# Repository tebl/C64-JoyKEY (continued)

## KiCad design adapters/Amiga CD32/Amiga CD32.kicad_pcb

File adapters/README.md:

# Adapters
Instead of adding a ton of jumpers to the module with the aim of accounting for every system known to man, I instead chose to leave those details up to the adapter. For more specific information, see the [adapters](https://github.com/tebl/C64-JoyKEY/blob/main/documentation/adapters.md) document available as part of the documentation (mostly to avoid having to maintain two copies of the same information).

For BOM, parts needed on putting it together is found in the relevant subfolder READMEs.

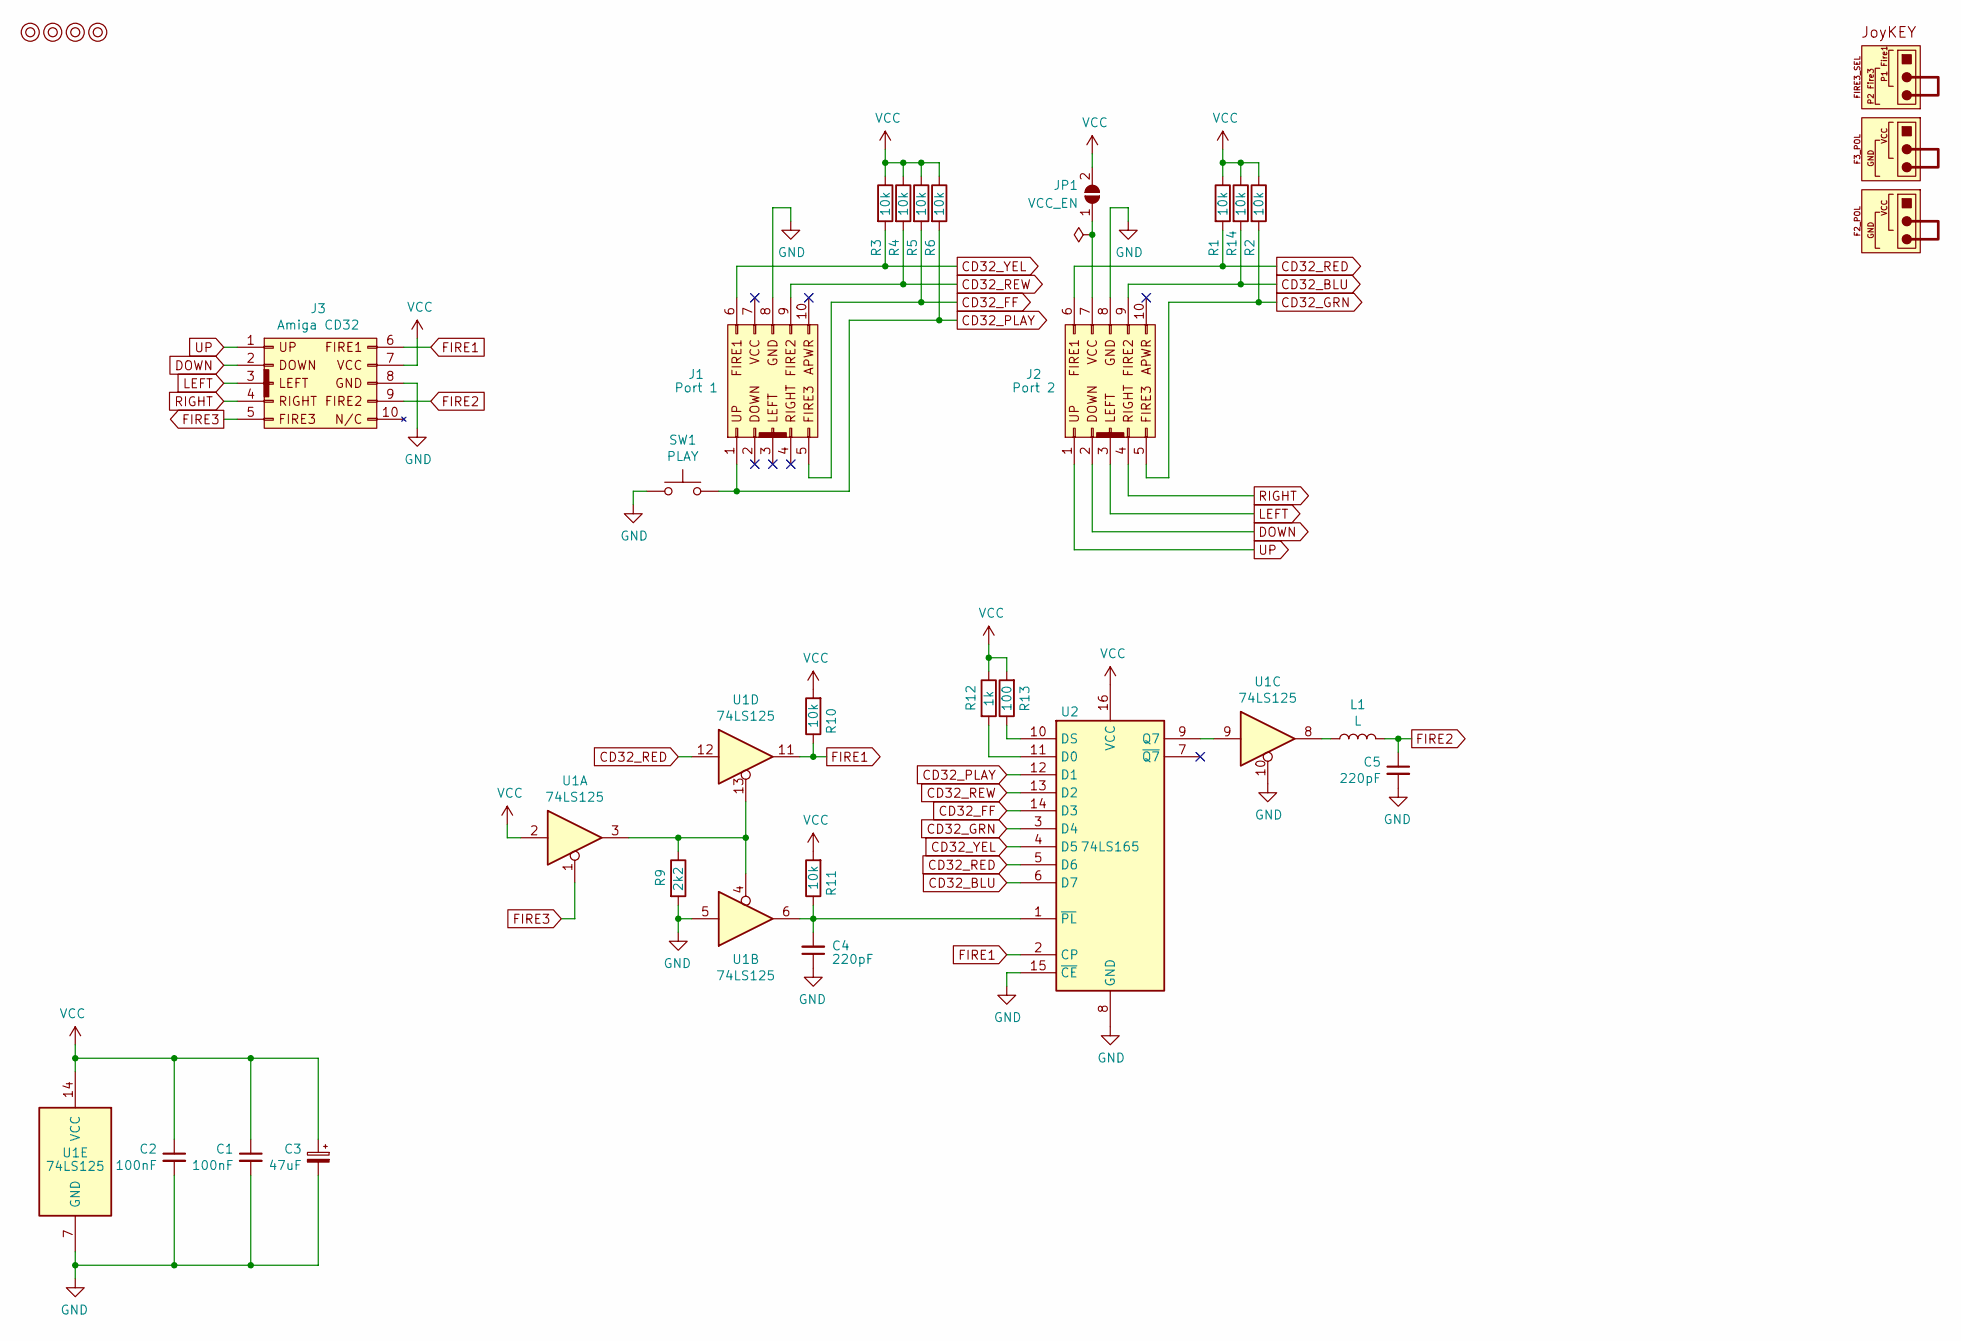
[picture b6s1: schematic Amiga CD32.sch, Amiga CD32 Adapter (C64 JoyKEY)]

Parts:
C1, C2: 100nF; C_Disc_D4.7mm_W2.5mm_P5.00mm
C3: 47uF; CP_Radial_D5.0mm_P2.00mm
C4, C5: 220pF; C_Disc_D4.7mm_W2.5mm_P5.00mm
J1: Port 1; IDC_Joystick
J2: Port 2; IDC_Joystick
J3: Amiga CD32; IDC_Joystick
JP1: VCC_EN; bridge_r
L1: L; L_Axial_L6.6mm_D2.7mm_P10.16mm_Horizontal_Vishay_IM-2
M1, M2, M3, M4: Mounting; M3_pin
R1, R3, R4, R11, R14: 10k; R_Axial_DIN0207_L6.3mm_D2.5mm_P10.16mm_Horizontal
R2, R5, R6, R10: 10k; R_Axial_DIN0207_L6.3mm_D2.5mm_P7.62mm_Horizontal
R9: 2k2; R_Axial_DIN0207_L6.3mm_D2.5mm_P7.62mm_Horizontal
R12: 1k; R_Axial_DIN0207_L6.3mm_D2.5mm_P7.62mm_Horizontal
R13: 100; R_Axial_DIN0207_L6.3mm_D2.5mm_P7.62mm_Horizontal
SW1: PLAY; SW_PUSH_6mm
U1: 74LS125; DIP-14_W7.62mm_Socket_LongPads
U2: 74LS165; DIP-16_W7.62mm_Socket_LongPads

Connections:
CD32_BLU: J2.9, R14.2, U2.6 (D7)
CD32_FF: J1.5, R5.2, U2.14 (D3)
CD32_GRN: J2.5, R2.2, U2.3 (D4)
CD32_PLAY: J1.1, R6.2, SW1.2, U2.12 (D1)
CD32_RED: J2.6, R1.2, U1.12, U2.5 (D6)
CD32_REW: J1.9, R4.2, U2.13 (D2)
CD32_YEL: J1.6, R3.2, U2.4 (D5)
DOWN: J2.2, J3.2
FIRE1: J3.6, R10.1, U1.11, U2.2 (CP)
FIRE2: C5.1, J3.9, L1.1
FIRE3: J3.5, U1.1
GND: C1.2, C2.2, C3.2, C4.1, C5.2, J1.8, J2.8, J3.8, R9.2, SW1.1, U1.5, U1.7 (GND), U1.10, U2.8 (GND), U2.15 (~CE)
LEFT: J2.3, J3.3
unnamed: C4.2, R11.1, U1.6, U2.1 (~PL)
unnamed: J2.7, JP1.1 (A)
unnamed: L1.2, U1.8
unnamed: R9.1, U1.3, U1.4, U1.13
unnamed: R12.2, U2.11 (D0)
unnamed: R13.1, U2.10 (DS)
unnamed: U1.9, U2.9 (Q7)
RIGHT: J2.4, J3.4
UP: J2.1, J3.1
VCC: C1.1, C2.1, C3.1, J3.7, JP1.2 (B), R1.1, R2.1, R3.1, R4.1, R5.1, R6.1, R10.2, R11.2, R12.1, R13.2, R14.1, U1.2, U1.14 (VCC), U2.16 (VCC)

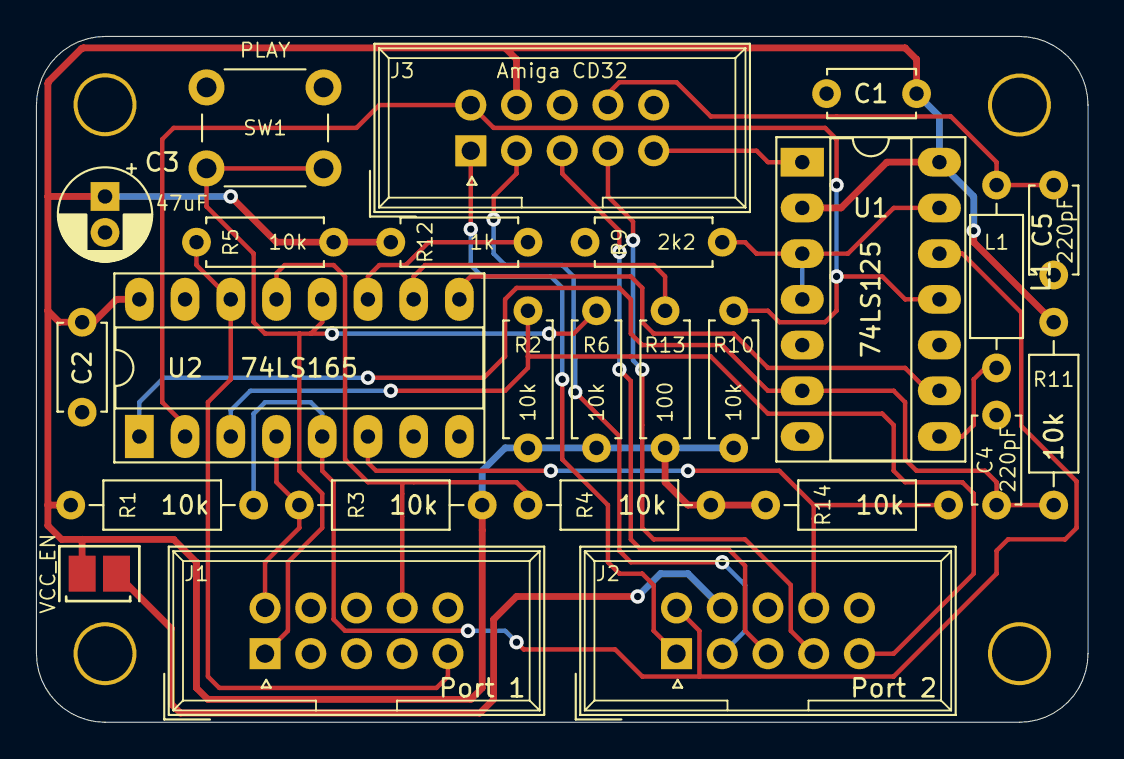
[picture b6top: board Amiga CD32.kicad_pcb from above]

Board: 2 copper layers, 58.4 x 38.1 mm, 29 parts (0 on the bottom side), 23 nets.

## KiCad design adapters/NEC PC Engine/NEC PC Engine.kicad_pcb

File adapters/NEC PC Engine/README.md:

# JoyKEY (NEC PC Engine)

**UNTESTED**

The NEC PC Engine, primarily found in the japanese markets as well as everywhere fans of the shoot em up genre could be found, had several revisions and third party controllers though most stuck with the regular four button configuration (*I*, *II*, *RUN* and *SELECT*). A picture of the completed adapter has been included below, including the jumpers needed on the *C64 JoyKEY* device itself. Making on requires a cable with the right shape, the simplest way of obtaining these is either cutting up a cheap extension cables.

# BOM
The parts listed are the ones I've used when building a Nintendo Entertainment System controller adapter for the *C64 JoyKEY*, part listed in parenthesis are considered optional (meaning you could build a more limited version of it).

| Reference     | Item                                      | Count | Order  |
| ------------- | ----------------------------------------- | ----- | ------ |
| PCB           | Fabricate using Gerber files              |     1 | PCBway
| C1            | 100nF ceramic capacitor (5mm)             |     1 |
| C3            | 10uF electrolytic capacitor 16v (4x2mm)   |     1 |
| J1,J2 *       | 2x5 pin straight header pins or 2x5 IDC   |     2 |
| J3            | 8 pin mini DIN with cable                 |     1 |
| JP1           | 2-pin breakable header pins (w/jumpers)   |    (1)|
| R1-R10        | 47k ohm resistor                          |    10 | 
| R11-R14       | 330 ohm resistor                          |     4 | 
| U1            | 74HC157 (DIP-16)                          |     1 |

*) Breakable dual row pin headers can be used here, but I find it is nicer to use a 2x5 pin connector here instead. The cable needed is a 2x5 pin IDC cable (usually listed as *AVR* or *JTAG* cable) with sufficient length, these are used with all adapters.

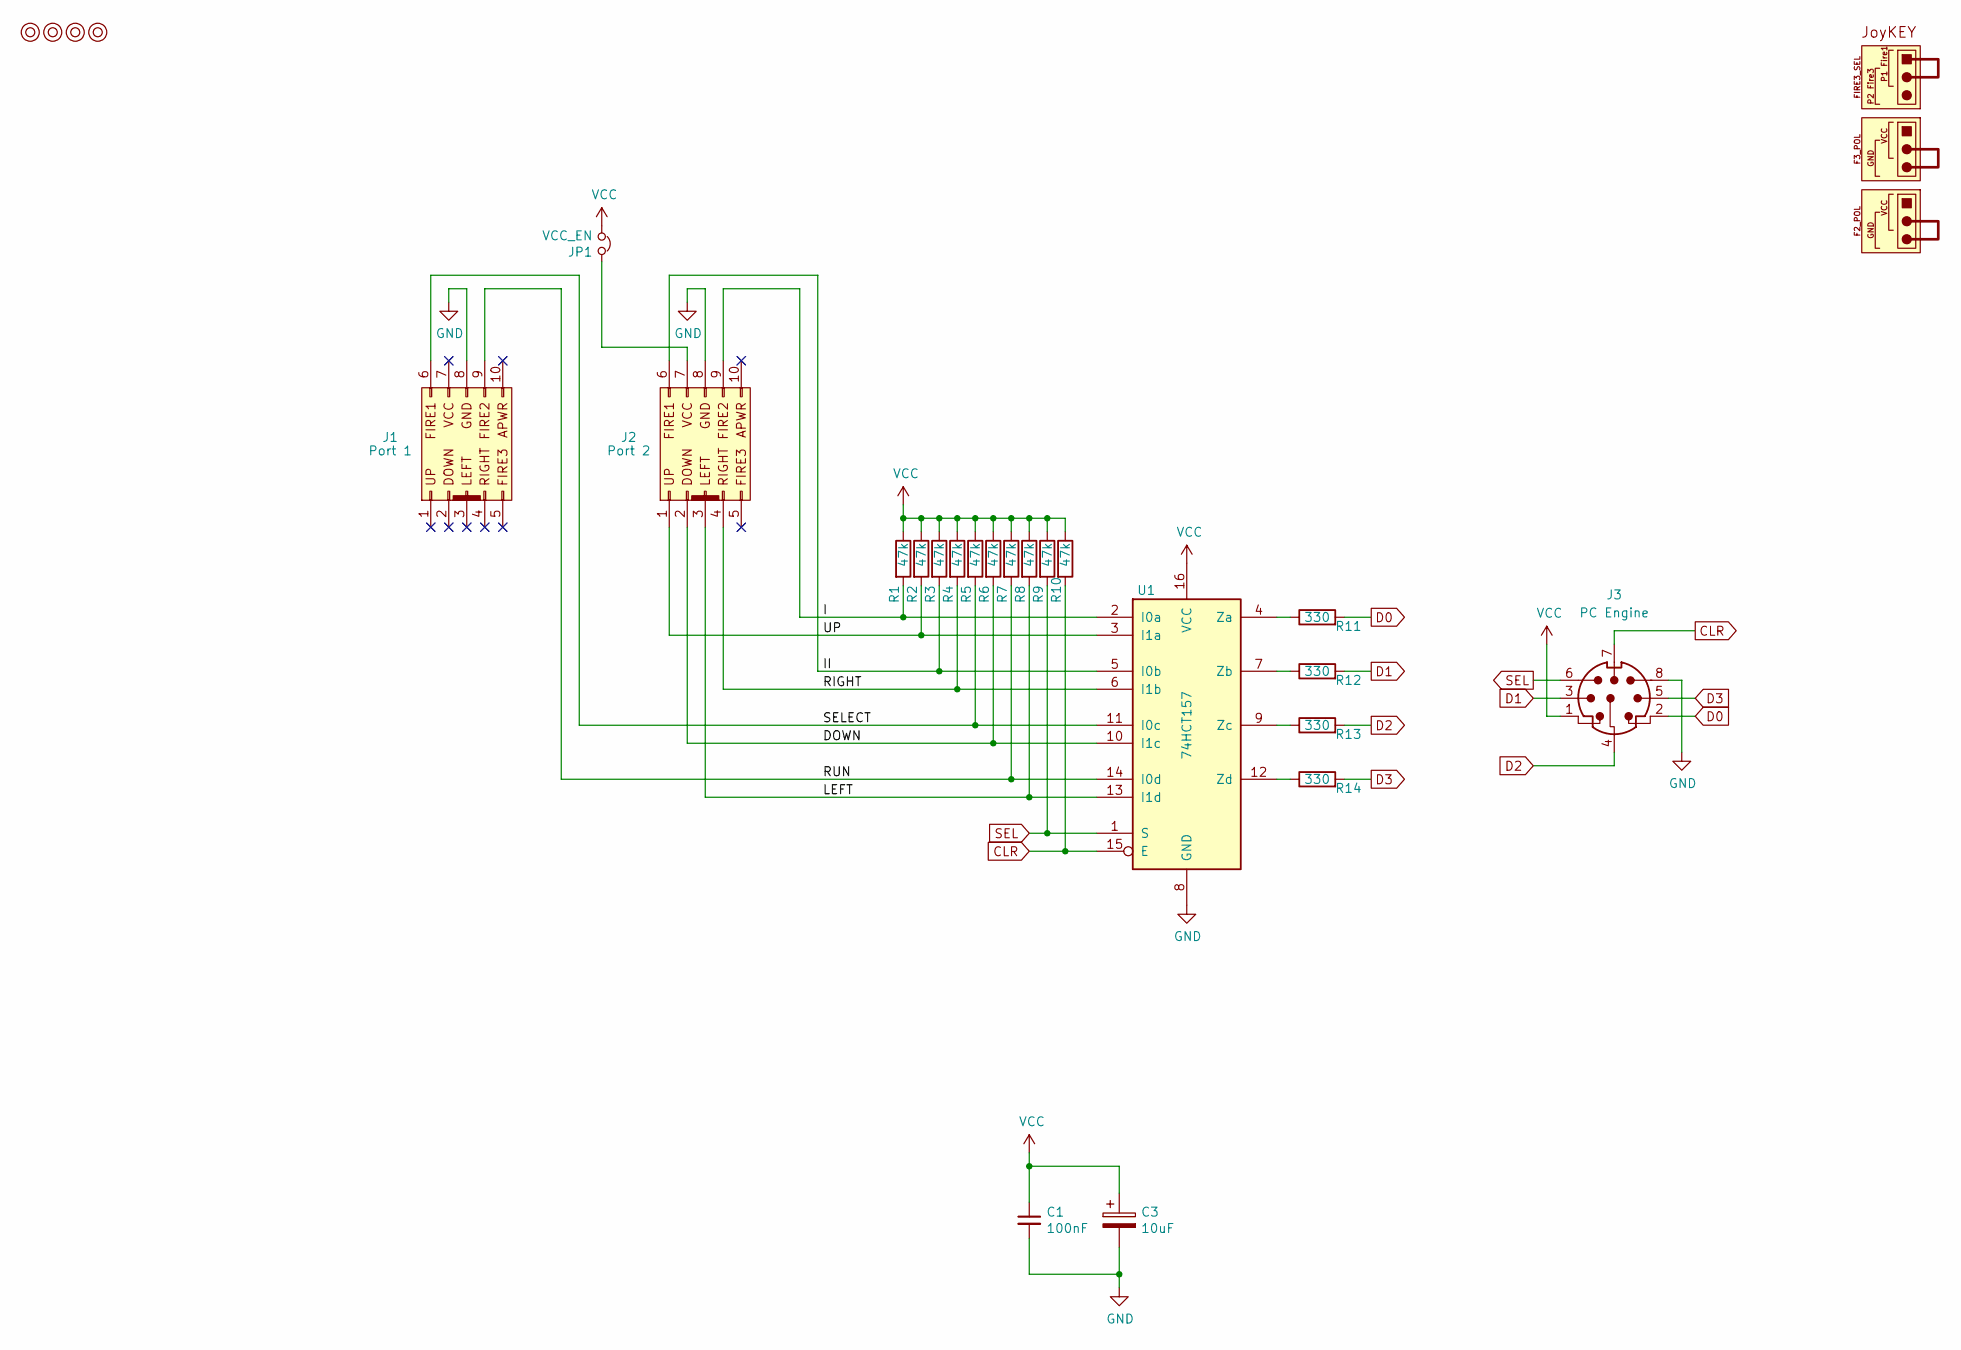
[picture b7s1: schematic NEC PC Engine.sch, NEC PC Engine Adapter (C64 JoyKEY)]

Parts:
C1: 100nF; C_Disc_D4.7mm_W2.5mm_P5.00mm
C3: 10uF; CP_Radial_D4.0mm_P2.00mm
J1: Port 1; IDC_Joystick
J2: Port 2; IDC_Joystick
J3: PC Engine; NEC_Output
JP1: VCC_EN; PinHeader_1x02_P2.54mm_Vertical
M1, M2, M3, M4: Mounting; M3_pin
R1, R2, R3, R4, R5, R6, R7, R8, R9, R10: 47k; R_Axial_DIN0207_L6.3mm_D2.5mm_P10.16mm_Horizontal
R11, R12, R13, R14: 330; R_Axial_DIN0207_L6.3mm_D2.5mm_P10.16mm_Horizontal
U1: 74HCT157; DIP-16_W7.62mm_Socket_LongPads

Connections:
/DOWN: J2.2, R6.2, U1.10 (I1c)
/I: J2.9, R1.2, U1.2 (I0a)
/II: J2.6, R3.2, U1.5 (I0b)
/LEFT: J2.3, R8.2, U1.13 (I1d)
/RIGHT: J2.4, R4.2, U1.6 (I1b)
/RUN: J1.9, R7.2, U1.14 (I0d)
/SELECT: J1.6, R5.2, U1.11 (I0c)
/UP: J2.1, R2.2, U1.3 (I1a)
CLR: J3.7 (CLR), R10.2, U1.15 (E)
D0: J3.2 (D0), R11.2
D1: J3.3 (D1), R12.2
D2: J3.4 (D2), R13.2
D3: J3.5 (D3), R14.2
GND: C1.2, C3.2, J1.8, J2.8, J3.8 (GND), U1.8 (GND)
unnamed: J2.7, JP1.1
unnamed: R11.1, U1.4 (Za)
unnamed: R12.1, U1.7 (Zb)
unnamed: R13.1, U1.9 (Zc)
unnamed: R14.1, U1.12 (Zd)
SEL: J3.6 (SEL), R9.2, U1.1 (S)
VCC: C1.1, C3.1, J3.1 (VCC), JP1.2, R1.1, R2.1, R3.1, R4.1, R5.1, R6.1, R7.1, R8.1, R9.1, R10.1, U1.16 (VCC)

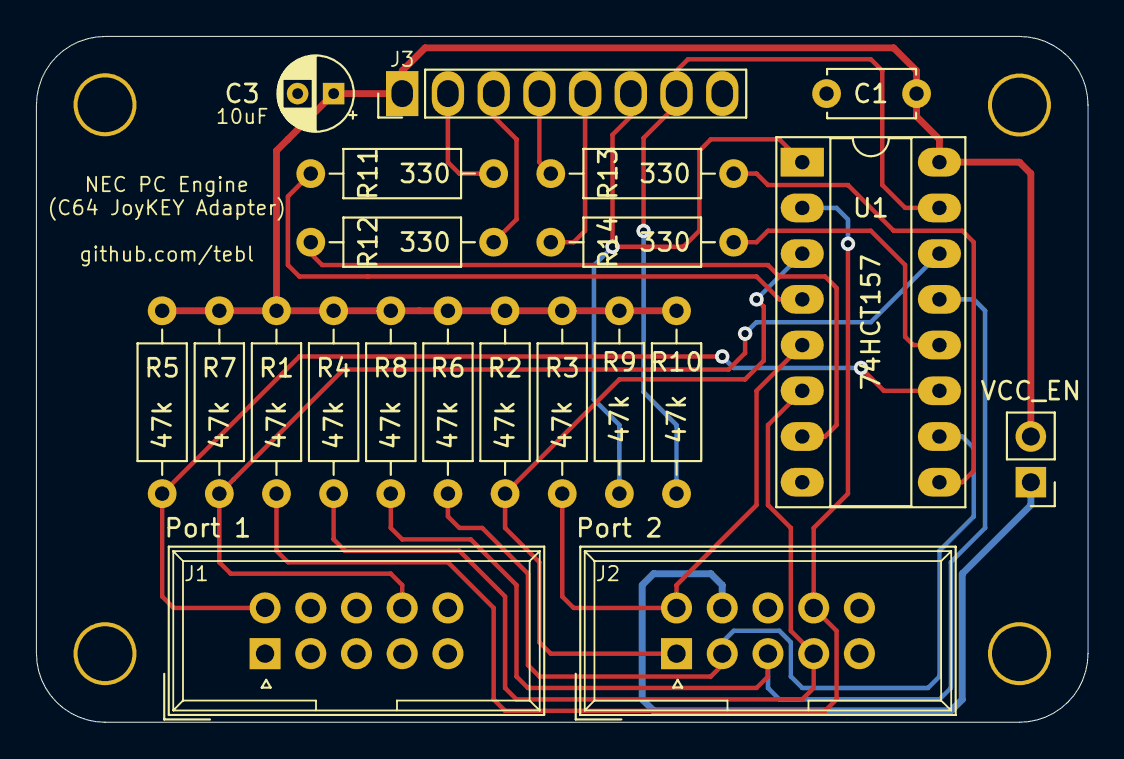
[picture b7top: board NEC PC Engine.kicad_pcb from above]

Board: 2 copper layers, 58.4 x 38.1 mm, 25 parts (0 on the bottom side), 21 nets.

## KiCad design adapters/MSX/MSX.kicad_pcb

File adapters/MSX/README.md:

# JoyKEY (MSX)

**UNTESTED**

The MSX-line of computers generally tried to be everything for everyone, as long as they wanted an 8bit computers. This meant a lot of different features going into it, including the surprisingly complicated joystick ports - designed to fit just about any device as long as it conformed to their very specific standard. Which means that it works with the standard Atari-style joystick, but if you want a second fire button or something that'd work reliable for joysticks requiring power you'll need an adapter in between. I was tempted to make this a more general adapter, but I couldn't point you to a specific joystick that'd work with it - unless you build it yourself, of course.

# BOM
The parts listed are the ones I've used when building a MSX adapter for use with the *C64 JoyKEY*, part listed in parenthesis are considered optional (meaning you could build a more limited version of it). 

| Reference     | Item                                      | Count | Order   |
| ------------- | ----------------------------------------- | ----- | ------- |
| PCB           | Fabricate using Gerber files              |    (1)| PCBway
| J1 *          | 2x5 pin straight header pins or 2x5 IDC   |     1 |
| J2 **         | DE-9 Female straight connector            |     1 |

*) Breakable dual row pin headers can be used here, but I find it is nicer to use a 2x5 pin connector here instead. The cable needed is a 2x5 pin IDC cable (usually listed as *AVR* or *JTAG* cable) with sufficient length.

**) These are the blue kind with straight pins, it will include a few metal bits on it - you'll need to do a test-fitting on your particular build of the MSX to determine if it can be left in place. If it feels like it'll break the socket, then you can remove the metal parts.

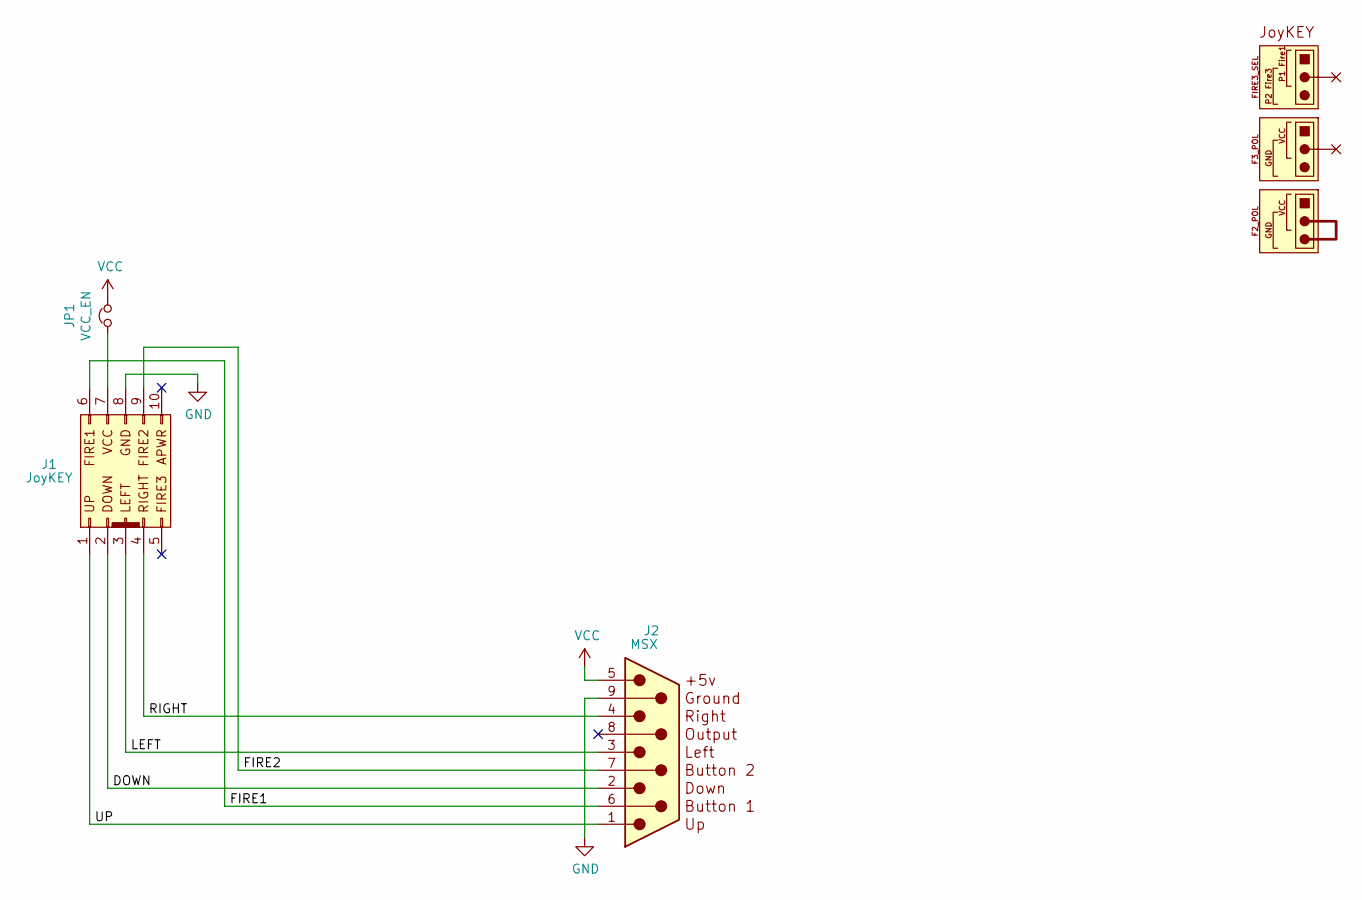
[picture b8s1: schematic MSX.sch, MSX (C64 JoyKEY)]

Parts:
J1: JoyKEY; IDC_Joystick
J2: MSX; DSUB-9_Female_Edge
JP1: VCC_EN; bridge

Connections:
/DOWN: J1.2, J2.2
/FIRE1: J1.6, J2.6
/FIRE2: J1.9, J2.7 (VCC)
/LEFT: J1.3, J2.3
/RIGHT: J1.4, J2.4
/UP: J1.1, J2.1
GND: J1.8, J2.9
unnamed: J1.7, JP1.1
VCC: J2.5, JP1.2

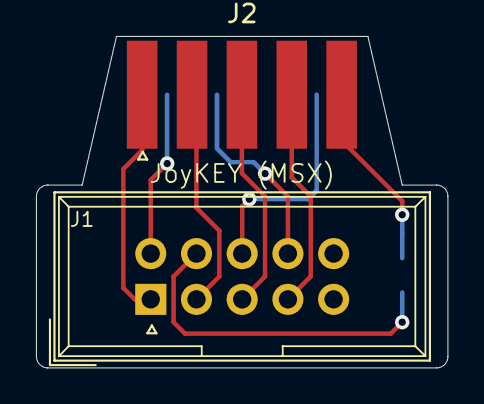
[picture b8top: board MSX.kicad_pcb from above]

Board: 2 copper layers, 22.9 x 18.4 mm, 3 parts (1 on the bottom side), 9 nets.

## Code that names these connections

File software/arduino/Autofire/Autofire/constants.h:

#ifndef _CONSTANTS_H
#define _CONSTANTS_H

/* 
 * Pin definitions 
 */
#define PIN_FIRE1 2
#define PIN_FIRE1_OUT 5
#define PIN_FIRE2 3
#define PIN_FIRE2_POL 21
#define PIN_FIRE3 4
#define PIN_FIRE3_POL 20
#define PIN_LEFT 14
#define PIN_RIGHT 18
#define PIN_UP 19
#define PIN_DOWN 15
#define PIN_UNDERGLOW 6
#define PIN_PWR 9
#define PIN_SYS 10

/* 
 * Definitions
 */
#define LED_OFF 0

#define KEY_MODE_DEFAULT 0
#define KEY_MODE_AUTOFIRE 1

#define JOYKEY_UP 0
#define JOYKEY_DOWN 1
#define JOYKEY_LEFT 2
#define JOYKEY_RIGHT 3
#define JOYKEY_FIRE1 4
#define JOYKEY_FIRE2 5
#define JOYKEY_FIRE3 6
#define NUM_KEYS 7

#define KEY_STATE_NEUTRAL 0
#define KEY_STATE_WAIT_RELEASE 1

const int KEY_PINS[NUM_KEYS] = { PIN_UP, PIN_DOWN, PIN_LEFT, PIN_RIGHT, PIN_FIRE1, PIN_FIRE2, PIN_FIRE3 };
#endif

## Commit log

2020-11-20 Schematic added
2020-11-22 Assign footprints
2020-11-22 Rough placement
2020-11-24 Routed tracks
2020-12-02 Arduino sketch added (incomplete)
2020-12-02 Added alternate keymap and changed key names
2020-12-03 Changed to track keys instead of doing repeat etc myself (allow OS to handle instead)
2020-12-03 Disable FIRE2/3 when polarity is set HIGH
2020-12-03 Added images
2020-12-03 Tweaked PCB layout
2020-12-04 Added joystick mode
2020-12-04 Added image
2020-12-04 Updated README to match
2020-12-04 Debounce joystick keys
2020-12-04 Added polarity notes
2020-12-05 Added second DEFAULT_FW so all buttons can be independent
2020-12-05 documentation placeholders
2020-12-05 README
2020-12-05 Rough draft on building
2020-12-05 Updated building document
2020-12-05 Added TOC
2020-12-05 Added firmware document
2020-12-05 Renamed images
2020-12-05 Added C64 to configuration
2020-12-05 Tweaked documents
2020-12-06 Fixed USB_FORCE_ALTERNATE
2020-12-06 Joystick mode should ignore disabled keys
2020-12-06 Autofire configuration
2020-12-06 Autofire sketch (untested)
2020-12-06 Rough sketch of autofire documentation
2020-12-06 Can disable LED flashing on autofire FW
2020-12-06 Added protection diodes
2020-12-07 Swapped jumper layout (need new pictures)
2020-12-07 Added series resistor to output pin
2020-12-07 Added USB-keyboard macros
2020-12-09 Changed key layout to match my keycaps
2020-12-10 New keycap pictures
2020-12-10 SMS cable schematic
2020-12-10 Moved JP3
2020-12-10 Added SMS jumper settings to schematic
2020-12-10 SMS Adapter PCB
2020-12-10 Added updated PDF schematic
2020-12-11 SMS*
2020-12-11 Added README
2020-12-13 Added untested Atari 7800 adapter
2020-12-15 Added a keycode mapping so that every key is a function key not on normal keyboard
2020-12-16 Added 5 second SYS shutoff
2020-12-16 Changed pictures to match new PCB
2020-12-16 Autofire PWR LED fades when not enabled
2020-12-16 Moved pictures, added parts to build instructions
2020-12-16 Added sideview
2020-12-16 Removed 006
2020-12-16 Added 006
2020-12-16 Added keycode hints to
2020-12-16 Adapter notice
2020-12-16 Increased LED_SEL pin separation to avoid shorts
2020-12-17 Gerber export
2020-12-17 Added PCBway links
2021-01-07 Updated silkscreen
2021-01-07 Updated A7800 silkscreen
2021-01-07 Added drill files
2021-01-07 Added adapter pictures
2021-01-08 Underglow LEDs added
2021-01-08 Updated gerbers for version C
2021-01-08 Tweaked faceplate
2021-01-08 Moved adapters into separate folder, added sinclair.
2021-01-08 Moved faceplates into separate folder.
2021-01-08 Updated B1 description
2021-01-08 Updated adapter READMEs
2021-01-09 Added some documentation here and there
2021-01-13 Minor tweaking
2021-01-13 Added more systems to the configuration section (some pictures missing)
2021-01-15 Added picture
2021-01-17 Added some more documentation
2021-01-17 Adapter order links added
2021-01-17 Added keycap notes
2021-01-19 Added straight 2x5 IDC to DB9 adapter
2021-01-19 Changed Q1 footprint
2021-01-19 Changed pinouts to match revision C
2021-01-19 Control underglow
2021-01-19 Increased LED_SEL spacing
2021-01-19 Flipped MX-switches
2021-01-19 Bigger LED cutout
2021-01-19 Faceplate B1 update
2021-01-20 Updated LED routines for PWM pins
2021-01-20 Added underglow effect
2021-01-20 Configure underglow separately from standard LEDs
2021-01-22 Arcade board schematic
2021-01-22 Added VCC_EN to IDC -> DB9 adapter
2021-01-22 Copied LED functions from main firmware
2021-01-24 Added pictures
2021-01-24 Changed magic combination image
2021-01-24 More images
2021-01-26 Default underglow to off for all modes, enable when required
2021-01-26 Enable underglow in USB mode
2021-01-26 Tweaked faceplate B1 cutouts to include LED
2021-01-29 Assigned arcade footprints
2021-01-29 Arcade board layout done
2021-02-01 Added underglow shutdown timer effect to fade on inactivity
2021-02-02 Last build images
2021-02-02 Added documentation
2021-02-02 Updated BOM to include underglow components
2021-02-02 Added override to force underglow on in default mode
2021-02-02 Added underglow image
2021-02-03 Blank B1
2021-02-03 Added C64 splash screen to A1
2021-02-04 Added UP_EN for direction
2021-02-04 Added Amiga to configuration
2021-02-05 Added CPC images
2021-02-05 Added Amstrad CPC configuration
2021-02-05 Added VCC_EN jumper
2021-02-05 Added ARD_EN jumper
2021-02-08 Fixed Sinclair adapter
2021-02-12 Allow arduino sketch to stay in default mode (skipping magic key detection)
2021-02-12 Tweaked sinclair adapter
2021-02-12 Added 10k resistors to isolate unpowered Arduino
2021-02-13 Play around with graphics
2021-02-19 Added male side to sinclair adapter
2021-02-20 Fixed Arcade pinout and added isolation for Arduino (need new layout)
2021-02-22 New arcade layout
2021-02-22 Silkscreen tweaked
2021-02-26 autofire had cycle lengths swapped
2021-02-26 Sega Mega Drive adapter, untested and incomplete
2021-02-27 Exported SMD alpha
2021-03-09 Changed underglow max
2021-03-09 Tweaked faceplates to allow more leeway on LEDs
2021-03-09 Blanked out B1
2021-03-11 Updated faceplate section with a short howto
2021-03-11 Sinclair system
2021-03-11 Sinclair adapter images
2021-03-11 Update README with latest adapter information
2021-03-12 Moved artwork files
2021-03-12 Artwork module README
2021-03-14 Disable Arduino RX/TX LEDs
2021-03-17 Updated ZX Spectrum +2/+3 adapter notes
2021-03-17 Some missing references
2021-03-20 SMD images
2021-03-20 Added Sega Mega Drive adapter details
2021-03-20 SMD Adapter README
2021-03-20 Changed Sinclair adapter description
2021-03-20 Updated PCBway shared links
2021-03-21 SkeletonKey
2021-03-27 Untested MSX adapter
2021-03-30 Notice untested
2021-03-30 Link MSX adapter
2021-03-30 Added arcade build pictures
2021-03-30 Swapped images
2021-03-30 More pictures
2021-03-30 Added arcade build instructions
2021-03-30 Added arcade references
2021-03-30 Added PCBway link
2021-04-14 Added some images
2022-01-27 Add discrete P1 switches
2022-01-28 Route new tracks and export gerbers
2022-02-20 Underglow and activity handled the same on USB and Joystick mode
2022-02-20 Boost mode
2022-02-20 Rev. E build images
2022-02-20 MSX adapter gerber export
2022-02-20 Fixed image
2022-02-20 Untested NES adapter
2022-02-20 NES listed
2022-02-21 Untested NEC PC Engine adapter
2022-03-05 Add strain relief
2022-04-22 Add NES pictures
2022-04-22 Updated NES adapter documentation
2022-04-22 Updated library
2022-04-25 MSX adapter image
2022-04-27 CD32 schematic
2022-04-27 Layout done
2022-04-27 Add entry
2022-04-27 Add schematic
2022-04-27 Add missing CD32 button
2022-04-27 Add one more button to arcade board
2022-05-22 Silkscreen tweaks
2022-08-06 List parts used
2023-01-26 Change recommended diode type to 1n5819 for lower voltage drop
2023-01-27 Untested gameport adapter
2023-01-27 Jumpers
2023-02-21 Fixed pin linked to VCC
2023-02-21 Trying out different circuit
2024-03-17 Different gameport circuit
2024-10-16 Gameport adapter that doesn't work
2024-10-16 Attempt update to KiCAD8
2024-10-16 Update typos
2024-10-19 2040 schematic drafted
2024-10-21 First layout drafted
2024-10-22 Update to KiCAD8
2024-10-25 Arcade 2040, and some cleanup
2024-11-03 Build images etc...
2024-11-06 SDL Gamecontroller entry (for customization)
2024-11-06 Add diode for power from USB
2024-11-08 BOM in CSV
2024-11-09 Try adding underglow to GPIO15
2024-11-22 Build tweaks to include LED labels
2024-11-27 GP2040 setup details
2024-11-27 Slight build tweaks for clarity
2024-11-27 Wrong schematic page size
2024-11-27 thec64 stick
2024-12-19 Evercade needs more buttons
2024-12-21 Change expansion header to JST XH, but in a right-angle variant
2024-12-21 Bottom plate
2024-12-31 last build updated
2024-12-31 More consistent footprint
2024-12-31 Add images
2024-12-31 Adapter 9 from 2040, first draft
2024-12-31 Slight tweaks
2025-01-03 Tweaked for cosmetics
2025-01-03 PCBway order number placeholder
2025-01-10 Larger labels
2025-01-10 Move gp2040 screenshots
2025-01-12 Add build images
2025-01-12 Evercade recommended pinout
2025-01-13 Small tweaks to documentation
2025-01-13 Add image
2025-01-13 It begins...
2025-01-14 ... it completes the documentation
2025-01-14 Documenting more things
2025-01-14 Remove link
